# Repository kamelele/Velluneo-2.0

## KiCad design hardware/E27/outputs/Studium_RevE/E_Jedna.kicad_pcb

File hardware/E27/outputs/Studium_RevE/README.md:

# Velluneo E27 · Rev E · studium gabarytów zasilacza

Dwa układy rozmieszczenia wykonane w KiCad na podstawie elektrycznej Rev D. Oba zachowują wartości i połączenia oryginalnych elementów. [Rev D 96 × 34 mm z plikami do wyceny JLCPCB](../Zasilacz_RevD_JLCPCB/README.md) pozostaje jako punkt odniesienia i wersja rezerwowa.

## Jedna płytka

**74 × 32 mm**, czyli ok. **27% mniej powierzchni** niż Rev D. Wszystkie 93 obrysy, łącznie z punktami testowymi, zmieściły się na dwóch stronach z tymi samymi obudowami. Pas pomiędzy padami sieci pierwotnych i wtórnych w rzucie na oś X ma **8,2 mm**. Pole miedzi odprowadzające ciepło trzeba zaprojektować ponownie wraz ze ścieżkami. [Płytka w KiCad](E_Jedna.kicad_pcb)

## Dwie płytki

- **57 × 32 mm, moc.** Wejście 230 V, przetwornica i transformator, prostownik wtórny D7 oraz kondensator wyjściowy C6. D7 i C6 pozostają na tej samej płytce co transformator. J101 wyprowadza S_RAW i S_RTN za układem pomiaru prądu. Pas między padami P/S wynosi 8,2 mm. [Płytka mocy w KiCad](E_Moc.kicad_pcb) · [Podgląd 3D](Podglady/RevE_plytka_mocy.png)
- **30 × 26 mm, sterowanie.** J102 przyjmuje wyłącznie wtórne 26 V i jego powrót. Na tej płytce są eFuse, dwa regulatory prądu, pomiar K1/K2, zatrzask zwarciowy, blokady i punkty testowe. J101/J102 mają zgodne przypisanie: pad 1 S_RAW, pad 2 S_RTN. Docelowy przewód i jego odciążenie wymagają projektu wraz z korpusem. [Płytka sterowania w KiCad](E_Sterowanie.kicad_pcb) · [Podgląd 3D](Podglady/RevE_plytka_sterowania.png)

Podział skraca najdłuższą płytkę o 17 mm względem wariantu jednopłytkowego. Łączna powierzchnia laminatu to 2604 mm² wobec 2368 mm² jednej płytki, czyli około 10% więcej. Zyskiem jest możliwość niezależnego rozmieszczenia części mocy i sterowania. Przy ułożeniu warstwowym trzeba sprawdzić odstęp pomiędzy sieciowymi obszarami i płytką sterowania w trzech wymiarach, przestrzeń na wiązkę i chłodzenie. Wycena wymagałaby dwóch projektów PCB, a dwustronne obsadzenie każdego obrysu osobnej weryfikacji panelu. [JLCPCB PCBA](https://jlcpcb.com/capabilities/pcb-assembly-capabilities)

## Co ogranicza zejście do 38 × 17 × 15 mm

Przyjęty transformator EE16 ma obwiednię montażową ok. 17,2 × 16,2 mm. W zachowanej orientacji i z 0,75 mm rezerwy od krawędzi po obu stronach sam potrzebuje około 17,7 mm szerokości. Poza transformatorem trzeba zmieścić obudowy po obu stronach bariery i zapewnić miejsce na bezpieczne prowadzenie ścieżek. Pionowo ustawiony warystor TMOV14 może wymagać do 22 mm nad PCB przy prostych wyprowadzeniach. Zmniejszanie obrysu z tym samym zestawem części nie rozwiązuje wysokości. [Obwiednia T1](E27.pretty/EE16_6pins_RFQ.kicad_mod) · [Wymiary TMOV, str. 6](https://www.littelfuse.com/assetdocs/varistors-tmov-datasheet?assetguid=bd475732-1071-4352-b8aa-f78b0007eb05)

Przy sztywnym celu 38 × 17 × 15 mm kolejny krok to wstępny dobór węższego i niższego transformatora wraz z izolacją oraz sprawdzenie ułożenia warystora i kondensatorów. Rozmieszczenie płytki mocy zależy od tych danych. Jeżeli korpus daje dwie oddzielne przestrzenie, punktem wyjścia do tej próby jest wariant z dwiema płytkami. Na makietach nie wykonano trasowania, wypełnień cieplnych, pomiarów ani eksportu do zamówienia. [Kontrola rozmieszczenia i przypisań pinów](Kontrola_RevE.md)

## Podglądy 3D

Dwie płytki we wspólnej scenie KiCad, w dwóch ujęciach wzorowanych na prezentacji JLCPCB. Oznaczenia i obrysy montażowe dodano na potrzeby podglądu. Widok bez elementów pokazuje rzeczywiste pady rozmieszczenia Rev E. Ścieżki są na dalszym etapie projektu. [Obie płytki z elementami](Podglady/RevE_JLC_obsadzone.png) · [Obie płytki z góry](Podglady/RevE_JLC_widok_PCB.png) · [Wzorzec JLCPCB](https://jlcpcb.com/blog/kicad-mcp-how-to-design-a-pcb-with-claude-code)

Poprzednie modele niestandardowych obudów w Rev D były prostymi bryłami zastępczymi. Dodałem własne modele do podglądu, z kształtem korpusów i wyprowadzeń. Obejmują m.in. warystor, kondensator Y1, dławik, kondensator SMD, bezpiecznik, mostek prostowniczy i układy scalone. Model transformatora odwzorowuje przyjętą obwiednię i układ sześciu wyprowadzeń, a wygląd rdzenia i uzwojenia pozostaje orientacyjny do wyboru dostawcy. Modele i materiały służą do wizualizacji. Do sprawdzenia mechaniki obowiązują rysunki wymiarowe i próbki komponentów. [Nichicon C6](https://www.nichicon.com/en-us/part/ucm1h471mnj1ms/2563/) · [Würth L1](https://www.we-online.com/components/products/datasheet/768772102.pdf) · [Vishay CY1](https://www.vishay.com/docs/23102/440lseries.pdf) · [Podgląd na stronie JLCPCB](https://jlcpcb.com/blog/kicad-mcp-how-to-design-a-pcb-with-claude-code)

[Rev D z nowymi modelami od góry](Podglady/RevD_nowe_modele_gora.png) · [Rev D od spodu](Podglady/RevD_nowe_modele_dol.png)

Z katalogu `hardware/E27` polecenie `work/export_reve.ps1` odtwarza modele 3D, podglądy i raporty. Opcja `-Rebuild` odtwarza również rozmieszczenie z pliku Rev D.

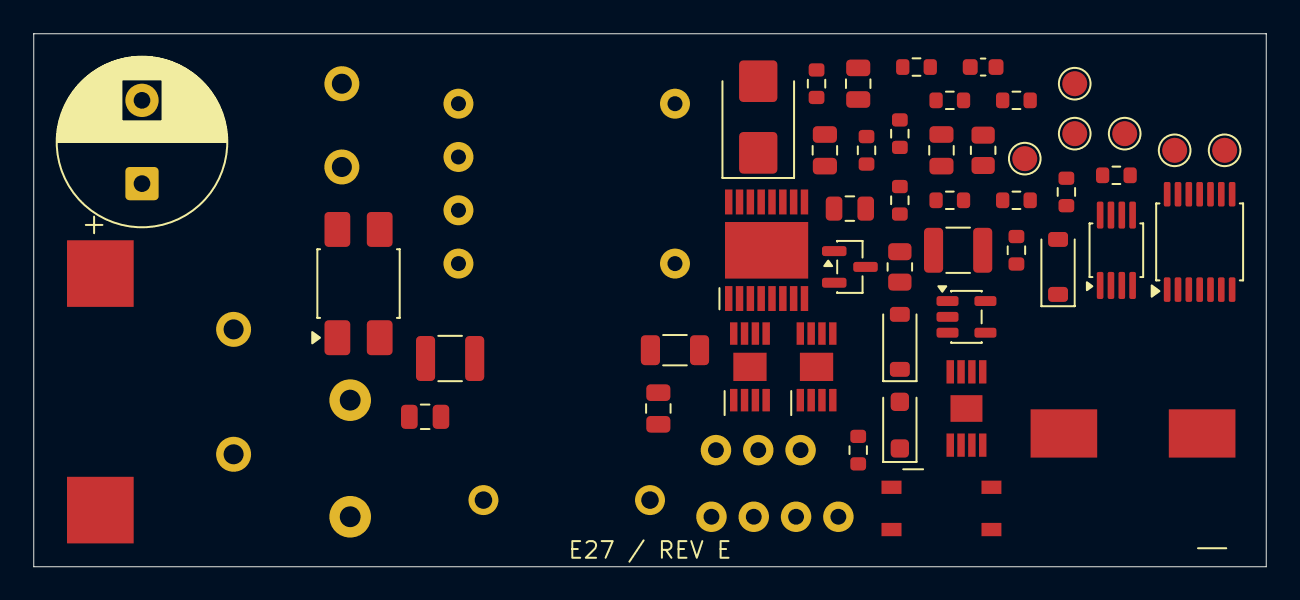
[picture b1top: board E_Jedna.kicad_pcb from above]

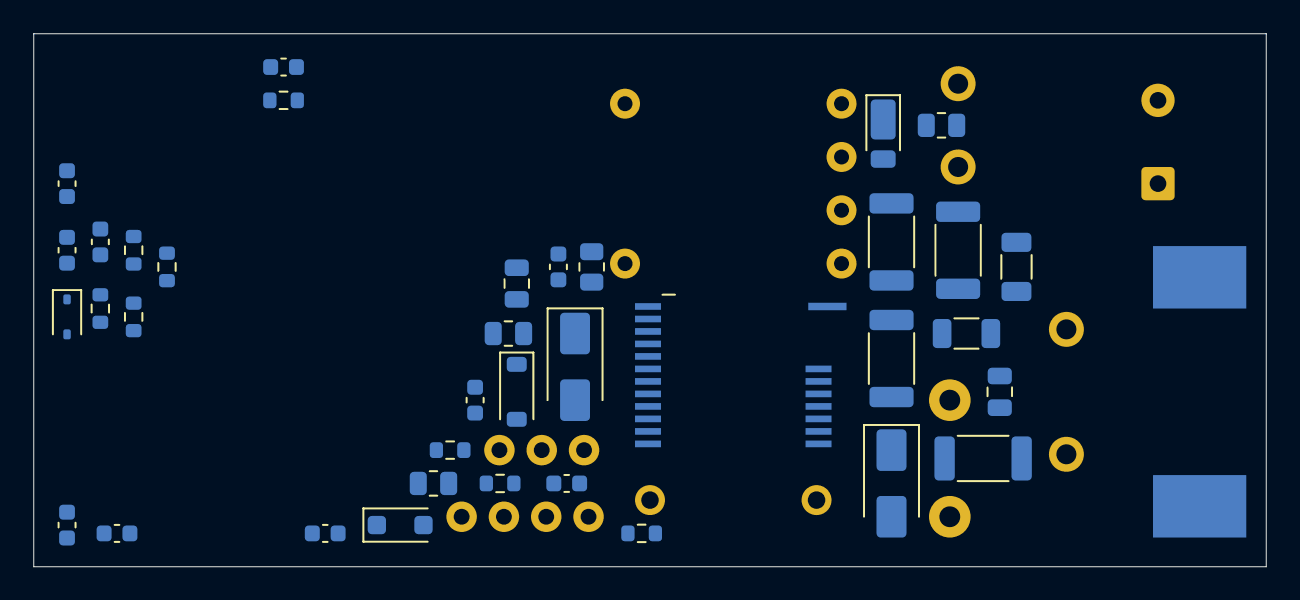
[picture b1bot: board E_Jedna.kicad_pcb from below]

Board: 2 copper layers, 74.0 x 32.0 mm, 93 parts (38 on the bottom side), 51 nets, no tracks yet.

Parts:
BR1: MB10S; OnSemi_751EP_SOIC-4_3.9x4.725mm_P2.54mm
C1: 100n / 630V; C_1210_3225Metric
C2: 10u / 450V; CP_Radial_D10.0mm_P5.00mm
C3: 1.5n / 200V; C_0805_2012Metric
C4: 22u / 35V; C_1206_3216Metric
C5: 470n / 50V; C_0805_2012Metric
C6: 470u / 50V; UCM_12p5
C7: 68p / 200V; C_0603_1608Metric
C8: 330p; C_0603_1608Metric
C9: 2.2u / 25V; C_1206_3216Metric
C10, C11, C13, C14, C15: 100n / 50V; C_0805_2012Metric
C12: 47n; C_0603_1608Metric
C101: 2.2u / 100V; C_1210_3225Metric
C102: 10u / 25V; C_0805_2012Metric
C103, C106, C108: 10n; C_0603_1608Metric
C104, C105: 220n / 50V X7R 10%; C_0603_1608Metric
C107, C109, C110: 100n; C_0603_1608Metric
CY1: 2.2n Y1; CY1_10mm
D5: US1J; D_SMA
D6: DFLU1200; D_PowerDI-123
D7: SK3200B; D_SMB
D8: US1B; D_SMA
D9: BAV21W; D_SOD-123
D101: BAT54WS; D_SOD-323
D102, D103: PMEG6010CEH; D_SOD-123F
F1: T 500 mA / 277 VAC; Schurter_UMT_H
J1: 230 VAC; Mains_L_N
J2: S1+TH / S2; Harness_4pos
J3: A+ / KA / KB; Harness_3pos
L1: 1mH; Wurth_TI_HV_8
Q1: MMBT5551; SOT-23
R1: 22R / 1.1W fusible; AC01_CS_WSZ
R2, R3: 510k HV; R_2010_5025Metric
R4: 1M; R_1206_3216Metric
R5, R19: 10k; R_0805_2012Metric
R6, R7: 2.2M HV; R_2010_5025Metric
R8: 47R; R_0805_2012Metric
R9: 0.11R; R_0805_2012Metric
R10: 110k 0.1%; R_0603_1608Metric
R11: 5.62k 0.1%; R_0603_1608Metric
R12: 2.2k; R_0805_2012Metric
R13: 100R; R_0805_2012Metric
R14: 226k 0.1%; R_0603_1608Metric
R15: 10k 0.1%; R_0603_1608Metric
R16: 30.1k 1%; R_0603_1608Metric
R17, R18: 10k; R_0603_1608Metric
R20, R21: 5.90k 1%; R_0603_1608Metric
R101, R109: 22k; R_0603_1608Metric
R102: 2.2k; R_0603_1608Metric
R103: 133k 0.1%; R_0603_1608Metric
R104, R106, R108: 22k 0.1%; R_0603_1608Metric
R105, R107: 330k 0.1%; R_0603_1608Metric
R110: 100k; R_0603_1608Metric
R111: 249R 1%; R_0603_1608Metric
R112: 100k 1%; R_0603_1608Metric
RV1: 275 VAC; TMOV14
T1: EE16 84:23:13; EE16_6pins_RFQ
TP101: S_RTN; TestPoint_Pad_D1.5mm
TP102: V3V3; TestPoint_Pad_D1.5mm
TP103: PG; TestPoint_Pad_D1.5mm
TP104: CLR_N; TestPoint_Pad_D1.5mm
TP105: PERMIT; TestPoint_Pad_D1.5mm
TP106: S_EN; TestPoint_Pad_D1.5mm
U1: LYT6073C-TL; InSOP_24D
U2: TPS26600PWPR; PWP0016A
U3, U4: AL5812MP-13; E27_Al5812_MSOP
U101: TPS7A1633; TPS7A16_DGN
U102: TLV1702; MSOP-8_3x3mm_P0.65mm
U103: SN74HCS74; TSSOP-14_4.4x5mm_P0.65mm
U104: SN74LVC1G132; SOT-23-5
U105: AQY212GS; AQY212GS_SOP4
ZD1: 18V; D_SOD-123
ZD2: 27V; D_SOD-123

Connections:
/CLK: C108.1, R110.2, U103.3
/CLR_N: D101.2, R109.2, TP104.1, U102.1, U102.7, U103.1
/DELAY: C103.1, U101.7
/EN_SERIES: R112.1, U105.3
/K1_F: C104.1, R105.2, R106.1, U102.2
/K2_F: C105.1, R107.2, R108.1, U102.6
/LDO_IN: C101.1, D102.1, D103.1, U101.5, U101.8
/LED_A: R111.2, U105.1
/LED_SINK: U104.4, U105.2
/PERMIT: TP105.1, U103.5, U104.2
/PG: D101.1, R101.2, R110.1, TP103.1, U101.3, U104.1
/P_0: BR1.2, C1.2, C2.2, C4.2, C5.2, R3.2, T1.4, U1.16, U1.17, U1.18, U1.19
/P_AUX: D6.2, T1.3
/P_BIAS: C4.1, D6.1, R5.1
/P_BLEED: R2.2, R3.1
/P_BPP: C5.1, R5.2, U1.14
/P_BR: BR1.1, C1.1, L1.1
/P_BULK: C2.1, C3.2, CY1.1, L1.2, R2.1, R4.2, R6.1, T1.2
/P_CL: C3.1, D5.1, R4.1
/P_D: D5.2, T1.1, U1.24
/P_L: F1.1, J1.1
/P_LF: F1.2, R1.1
/P_LR: BR1.3, R1.2, RV1.1
/P_N: BR1.4, J1.2, RV1.2
/P_V: R7.2, U1.13
/P_VMID: R6.2, R7.1
/REF: C106.1, R103.2, R104.1, U102.3, U102.5
/S1_RETURN: J2.2, U105.4
/S_BPS: C9.1, D9.1, U1.4
/S_EN: R18.1, R112.2, TP106.1, U2.7
/S_ENFEED: J2.1, R17.2
/S_FB: C8.1, R10.2, R11.1, U1.3
/S_FUSED: C13.1, J2.3, U2.15, U2.16
/S_FWD: C7.1, R8.2, U1.7
/S_GND: C6.2, C7.2, C8.2, C9.2, C10.2, D7.2, D8.1, R9.2, R11.2, U1.2, U1.5, ZD1.2
/S_ILIM: R16.1, U2.11
/S_LED_KA: J3.2, R105.1, U3.8
/S_LED_KB: J3.3, R107.1, U4.8
/S_LED_PLUS: C14.1, C15.1, J2.4, J3.1, R19.1, U3.1, U4.1
/S_OVA: R13.1, ZD2.2
/S_OVB: D9.2, R13.2
/S_OVP: R14.2, R15.1, U2.5
/S_RAW: C6.1, C11.1, CY1.2, D102.2, Q1.3, R10.1, R12.1, R14.1, R17.1, T1.5, U2.1, U2.2, ZD2.1
/S_RTN: C11.2, C12.2, C13.2, C14.2, C15.2, C101.2, C102.2, C103.2, C104.2, C105.2, C106.2, C107.2, C108.2, C109.2, C110.2, D8.2, R9.1, R15.2, R16.2, R18.2, R19.2, R20.2, R21.2, R102.2, R104.2, R106.2, R108.2, TP101.1, U1.1, U2.3, U2.8, U2.9, U2.17, U3.5, U3.9, U4.5, U4.9, U101.4, U101.9, U102.4, U103.7, U103.11, U103.12, U103.13, U104.3
/S_SET_A: R20.1, U3.4
/S_SET_B: R21.1, U4.4
/S_SLEW: C12.1, U2.12
/S_SW: D7.1, R8.1, T1.6
/S_VO: C10.1, Q1.2, U1.6
/S_Z18: Q1.1, R12.2, ZD1.1
/V3V3: C102.1, C107.1, C109.1, C110.1, D103.2, R101.1, R102.1, R103.1, R109.1, R111.1, TP102.1, U101.1, U102.8, U103.2, U103.4, U103.10, U103.14, U104.5

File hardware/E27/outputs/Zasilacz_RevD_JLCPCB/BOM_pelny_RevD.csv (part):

Ref,Nazwa i funkcja,Parametry,Producent,MPN,Footprint,LCSC Part #,Ilość na PCB,Zakup alternatywny,Cena jednostkowa prototyp / seria,Koszt pozycji prototyp / seria,Dostępność,Zamiennik do weryfikacji,Strona,Plan montażu,Źródło,Uwagi
J1,Przewody L i N z E27,230 VAC,,,E27:Mains_L_N,,1,Wycena dostawcy / RFQ,Do wyceny,Do wyceny,Brak potwierdzonego kodu w katalogu montażowym,,Top,Montaż wiązki po obsadzeniu,,THT / wiązka. Uzgodnić oddzielny montaż. Stałe lutowanie i odciążenie przewodów.
F1,Bezpiecznik zwłoczny,T 500 mA / 277 VAC,Schurter,3403.0271.23,E27:Schurter_UMT_H,,1,DigiKey 9094779,Do wyceny,Do wyceny,Brak potwierdzonego kodu w katalogu montażowym,,Bottom,RFQ / dobrać i zweryfikować dokładny MPN,https://www.digikey.com/en/products/detail/schurter-inc/3403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,"UMT-H. 1,5 kA przy 277 VAC UL albo przy 250 VAC IEC, warunki z karty. Wymaga testu zdolności wyłączania całego zespołu."
RV1,Ogranicznik przepięć z odcięciem termicznym,275 VAC,Littelfuse,TMOV14RP275E,E27:TMOV14,C1528070,1,Littelfuse / DigiKey,Do wyceny,Do wyceny,Zapas montażowy JLCPCB do potwierdzenia,iTMOV14RP275M z adaptacją footprintu i badaniem,Top,Osobne uzgodnienie montażu THT,https://jlcpcb.com/partdetail/Littelfuse-TMOV14RP275E/C1528070,"Za R1. Budżet wysokości 22 mm dla prostych wyprowadzeń. Sprawdzić udar, ciągłe przepięcie i rozłączenie termiczne."
R1,Ograniczenie prądu udarowego,22R / 1.1W fusible,Vishay,AC01000902209JBMCS,E27:AC01_CS_WSZ,,1,DigiKey 28721869,Do wyceny,Do wyceny,Brak potwierdzonego kodu w katalogu montażowym,,Top,RFQ / dobrać i zweryfikować dokładny MPN,https://www.digikey.com/en/products/detail/vishay-beyschlag-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,"AC01-CS WSZ. Potwierdzić obrys, impuls rozruchowy, temperaturę i koordynację z F1."
C1,Bocznik HF za mostkiem,100n / 630V,TDK,C3225X7T2J104KT000N,Capacitor_SMD:C_1210_3225Metric,C342668,1,LCSC / Mouser,Do wyceny,Do wyceny,Zapas montażowy JLCPCB do potwierdzenia,1210 100 nF 630 V po sprawdzeniu charakterystyki DC,Top,Do importu i sprawdzenia w JLCPCB,https://www.lcsc.com/product-detail/C342668.html,"SMT do potwierdzenia w JLCPCB po importowaniu BOM. X7T, sprawdzić pojemność pod napięciem DC."
L1,Dławik filtra różnicowego,1mH,Würth Elektronik,768772102,E27:Wurth_TI_HV_8,C7194056,1,DigiKey 2682552,Do wyceny,Do wyceny,Zapas JLCPCB do potwierdzenia. Poprzedni odczyt 0.,,Top,Osobne uzgodnienie montażu THT,https://jlcpcb.com/partdetail/WurthElektronik-768772102/C7194056,"1 mH, 0,5 A, Isat 0,55 A typ. Brak ekranu. Sprawdzić EMI, udar i rozgrzanie w rzeczywistym układzie."
C2,Magazyn energii na szynie HV,10u / 450V,Rubycon,450BXW10MEFR10X16,Capacitor_THT:CP_Radial_D10.0mm_P5.00mm,,1,DigiKey 6049847,Do wyceny,Do wyceny,Brak potwierdzonego kodu w katalogu montażowym,,Top,Osobne uzgodnienie montażu THT,https://www.digikey.com/es/products/detail/rubycon/450BXW10M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,"Ø10 mm × 16 mm nominalnie. 18 mm maks. nad PCB, raster 5 mm. 10 000 h przy 105°C."
R2,Rozładowanie szyny HV,510k HV,Vishay,CRCW2010510KFKEF,Resistor_SMD:R_2010_5025Metric,C4245382,1,Wycena dostawcy / RFQ,Do wyceny,Do wyceny,Zapas montażowy JLCPCB do potwierdzenia,,Bottom,Do importu i sprawdzenia w JLCPCB,https://www.lcsc.com/product-detail/C4245382.html,"Vishay CRCW2010, 400 V DC/RMS wg karty. Potwierdzić udar i rozkład napięcia. SMT do potwierdzenia w JLCPCB po importowaniu BOM. Dwa rezystory szeregowe, potwierdzić napięcie pracy, dobrać tolerancję i udar."
R3,Rozładowanie szyny HV,510k HV,Vishay,CRCW2010510KFKEF,Resistor_SMD:R_2010_5025Metric,C4245382,1,Wycena dostawcy / RFQ,Do wyceny,Do wyceny,Zapas montażowy JLCPCB do potwierdzenia,,Bottom,Do importu i sprawdzenia w JLCPCB,https://www.lcsc.com/product-detail/C4245382.html,"Vishay CRCW2010, 400 V DC/RMS wg karty. Potwierdzić udar i rozkład napięcia. SMT do potwierdzenia w JLCPCB po importowaniu BOM."
T1,Transformator flyback 1.2 mH ±8%,EE16 84:23:13,,,E27:EE16_6pins_RFQ,,1,Wycena dostawcy / RFQ,Do wyceny,Do wyceny,Brak potwierdzonego kodu w katalogu montażowym,,Top,RFQ transformatora EE16 i montaż THT,,"THT / wiązka. Uzgodnić oddzielny montaż. RFQ. Potwierdzić karkas, pinout, TIW, odstępy i badania. Zwroty w raporcie."
C3,Kondensator ogranicznika RCD,1.5n / 200V,KYOCERA AVX,08052C152KAT2A,Capacitor_SMD:C_0805_2012Metric,,1,"DigiKey / Mouser, wyszukiwanie po MPN",Do wyceny,Do wyceny,Brak potwierdzonego kodu w katalogu montażowym,"Element równoważny po sprawdzeniu wartości, obudowy, temperatury i parametrów impulsowych",Bottom,RFQ / dobrać i zweryfikować dokładny MPN,,SMT do potwierdzenia w JLCPCB po importowaniu BOM.
R4,Rezystor ogranicznika RCD,1M,Panasonic,ERJ-8GEYJ105V,Resistor_SMD:R_1206_3216Metric,C278663,1,"DigiKey / Mouser, wyszukiwanie po MPN",Do wyceny,Do wyceny,Zapas montażowy JLCPCB do potwierdzenia,"Element równoważny po sprawdzeniu wartości, obudowy, temperatury i parametrów impulsowych",Bottom,Do importu i sprawdzenia w JLCPCB,https://www.lcsc.com/product-detail/C278663.html,SMT do potwierdzenia w JLCPCB po importowaniu BOM.
D5,Dioda ogranicznika RCD,US1J,Diodes Inc.,US1J-13-F,Diode_SMD:D_SMA,C85095,1,"DigiKey / Mouser, wyszukiwanie po MPN",Do wyceny,Do wyceny,Zapas montażowy JLCPCB do potwierdzenia,"Element równoważny po sprawdzeniu wartości, obudowy, temperatury i parametrów impulsowych",Bottom,Do importu i sprawdzenia w JLCPCB,https://www.lcsc.com/product-detail/C85095.html,"SMT do potwierdzenia w JLCPCB po importowaniu BOM. Potwierdzić impulsy, temperaturę i rzeczywiste VDS."
D6,Prostownik uzwojenia pomocniczego,DFLU1200,Diodes Inc.,DFLU1200-7,Diode_SMD:D_PowerDI-123,,1,"DigiKey / Mouser, wyszukiwanie po MPN",Do wyceny,Do wyceny,Brak potwierdzonego kodu w katalogu montażowym,"Element równoważny po sprawdzeniu wartości, obudowy, temperatury i parametrów impulsowych",Bottom,RFQ / dobrać i zweryfikować dokładny MPN,,SMT do potwierdzenia w JLCPCB po importowaniu BOM.
C4,Zasobnik zasilania BPP,22u / 35V,TDK,C3216X5R1V226M160AC,Capacitor_SMD:C_1206_3216Metric,C69612,1,"DigiKey / Mouser, wyszukiwanie po MPN",Do wyceny,Do wyceny,Zapas montażowy JLCPCB do potwierdzenia,"Element równoważny po sprawdzeniu wartości, obudowy, temperatury i parametrów impulsowych",Bottom,Do importu i sprawdzenia w JLCPCB,https://www.lcsc.com/product-detail/C69612.html,SMT do potwierdzenia w JLCPCB po importowaniu BOM.
R5,Ograniczenie prądu zasilania BPP,10k,Panasonic,ERJ-6ENF1002V,Resistor_SMD:R_0805_2012Metric,C169253,1,"DigiKey / Mouser, wyszukiwanie po MPN",Do wyceny,Do wyceny,Zapas montażowy JLCPCB do potwierdzenia,"Element równoważny po sprawdzeniu wartości, obudowy, temperatury i parametrów impulsowych",Bottom,Do importu i sprawdzenia w JLCPCB,https://www.lcsc.com/product-detail/C169253.html,SMT do potwierdzenia w JLCPCB po importowaniu BOM.
R6,Pomiar napięcia szyny V,2.2M HV,Vishay,CRCW20102M20FKEF,Resistor_SMD:R_2010_5025Metric,C4263855,1,Wycena dostawcy / RFQ,Do wyceny,Do wyceny,Zapas montażowy JLCPCB do potwierdzenia,,Bottom,Do importu i sprawdzenia w JLCPCB,https://www.lcsc.com/product-detail/C4263855.html,"Vishay CRCW2010, 400 V DC/RMS wg karty. Potwierdzić udar i rozkład napięcia. SMT do potwierdzenia w JLCPCB po importowaniu BOM."
R7,Pomiar napięcia szyny V,2.2M HV,Vishay,CRCW20102M20FKEF,Resistor_SMD:R_2010_5025Metric,C4263855,1,Wycena dostawcy / RFQ,Do wyceny,Do wyceny,Zapas montażowy JLCPCB do potwierdzenia,,Bottom,Do importu i sprawdzenia w JLCPCB,https://www.lcsc.com/product-detail/C4263855.html,"Vishay CRCW2010, 400 V DC/RMS wg karty. Potwierdzić udar i rozkład napięcia. SMT do potwierdzenia w JLCPCB po importowaniu BOM."
C5,Odprzęganie BPP,470n / 50V,Murata,GRM21BR71H474KA88L,Capacitor_SMD:C_0805_2012Metric,C86043,1,"DigiKey / Mouser, wyszukiwanie po MPN",Do wyceny,Do wyceny,Zapas montażowy JLCPCB do potwierdzenia,"Element równoważny po sprawdzeniu wartości, obudowy, temperatury i parametrów impulsowych",Top,Do importu i sprawdzenia w JLCPCB,https://www.lcsc.com/product-detail/C86043.html,SMT do potwierdzenia w JLCPCB po importowaniu BOM.
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
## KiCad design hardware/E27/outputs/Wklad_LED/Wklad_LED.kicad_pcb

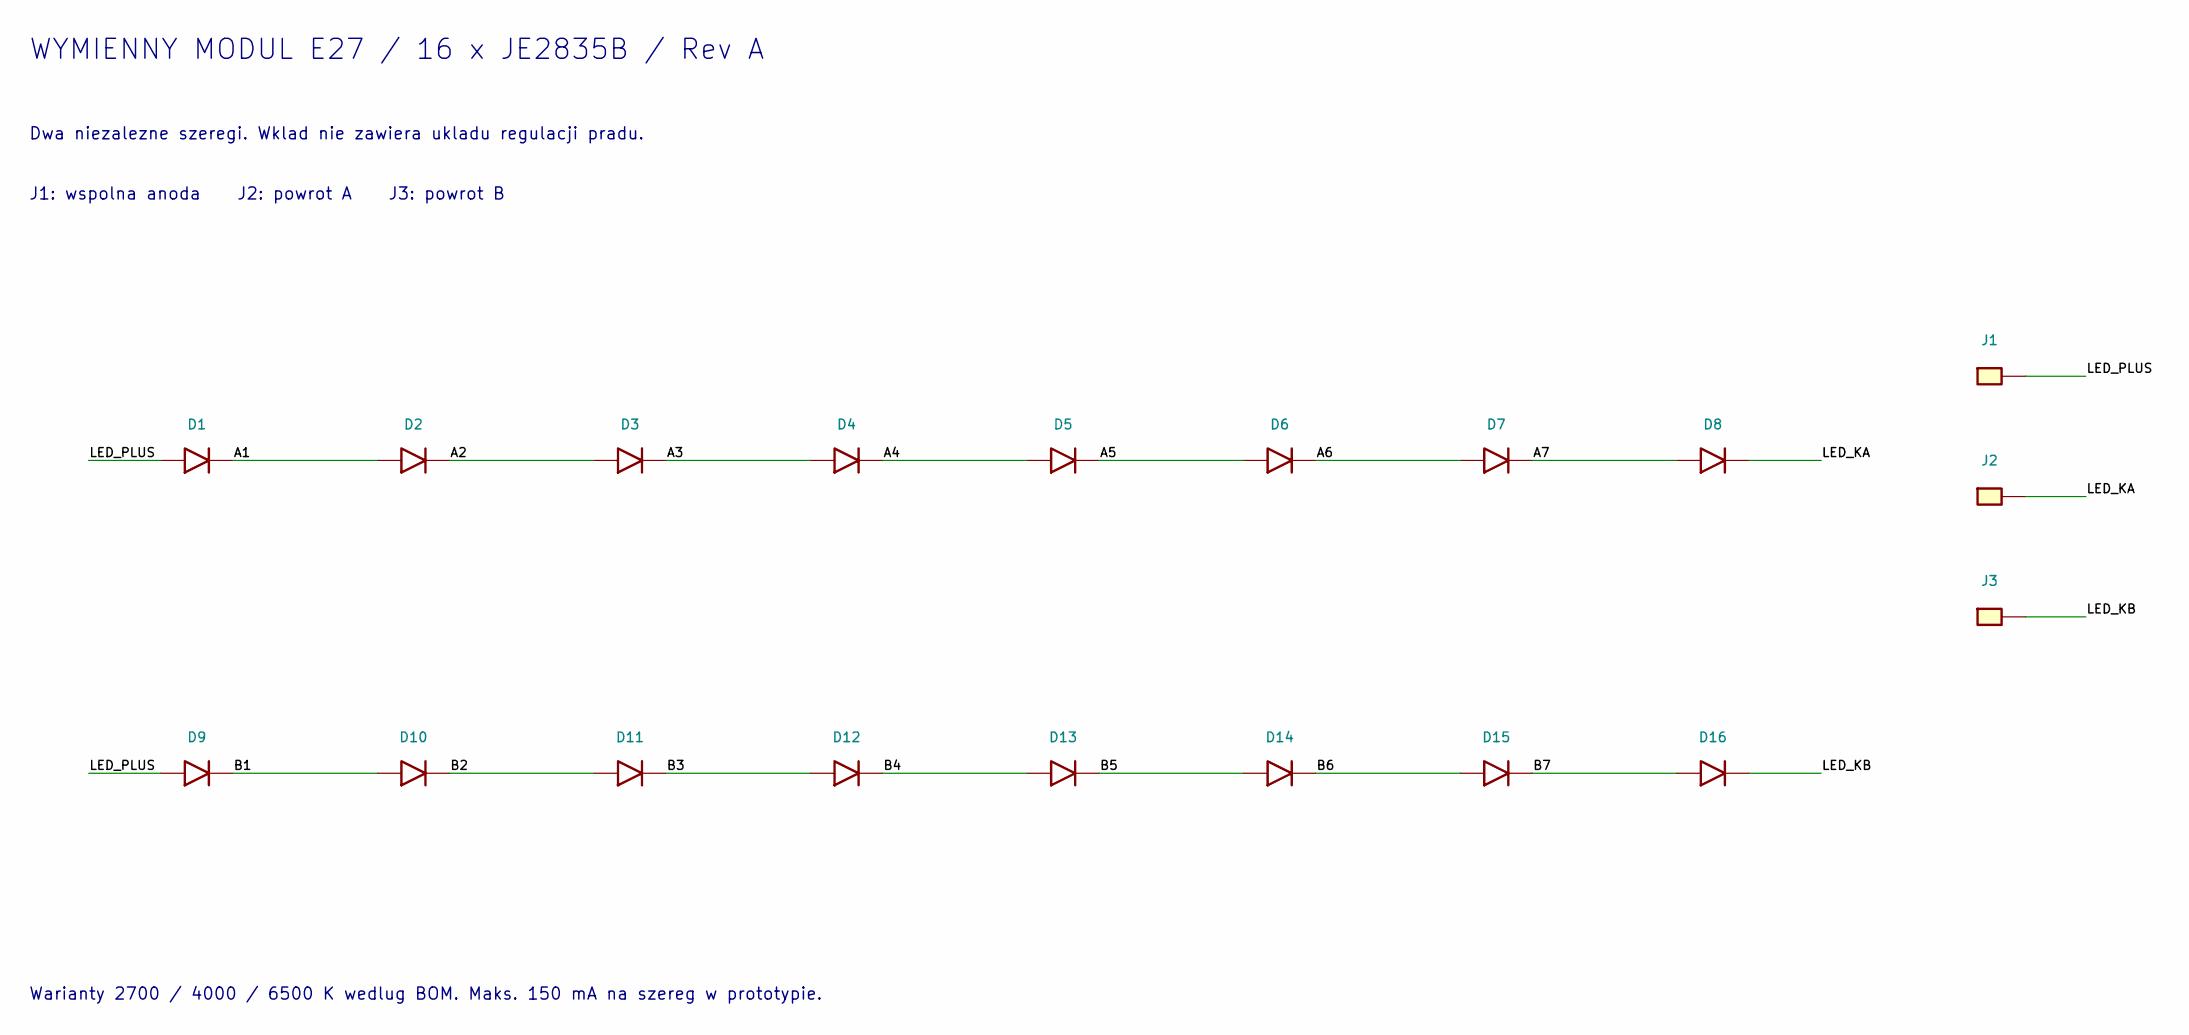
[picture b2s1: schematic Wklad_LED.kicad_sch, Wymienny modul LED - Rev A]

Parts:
D1, D2, D3, D4, D5, D6, D7, D8, D9, D10, D11, D12, D13, D14, D15, D16: JE2835B; Cree_JE2835B
J1: LED_PLUS; SpringPad
J2: LED_KA; SpringPad
J3: LED_KB; SpringPad

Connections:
/A1: D1.1 (K), D2.2 (A)
/A2: D2.1 (K), D3.2 (A)
/A3: D3.1 (K), D4.2 (A)
/A4: D4.1 (K), D5.2 (A)
/A5: D5.1 (K), D6.2 (A)
/A6: D6.1 (K), D7.2 (A)
/A7: D7.1 (K), D8.2 (A)
/B1: D9.1 (K), D10.2 (A)
/B2: D10.1 (K), D11.2 (A)
/B3: D11.1 (K), D12.2 (A)
/B4: D12.1 (K), D13.2 (A)
/B5: D13.1 (K), D14.2 (A)
/B6: D14.1 (K), D15.2 (A)
/B7: D15.1 (K), D16.2 (A)
/LED_KA: D8.1 (K), J2.1
/LED_KB: D16.1 (K), J3.1
/LED_PLUS: D1.2 (A), D9.2 (A), J1.1

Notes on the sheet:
WYMIENNY MODUL E27 / 16 x JE2835B / Rev A
Dwa niezalezne szeregi. Wklad nie zawiera ukladu regulacji pradu.
J1: wspolna anoda J2: powrot A J3: powrot B
Warianty 2700 / 4000 / 6500 K wedlug BOM. Maks. 150 mA na szereg w prototypie.

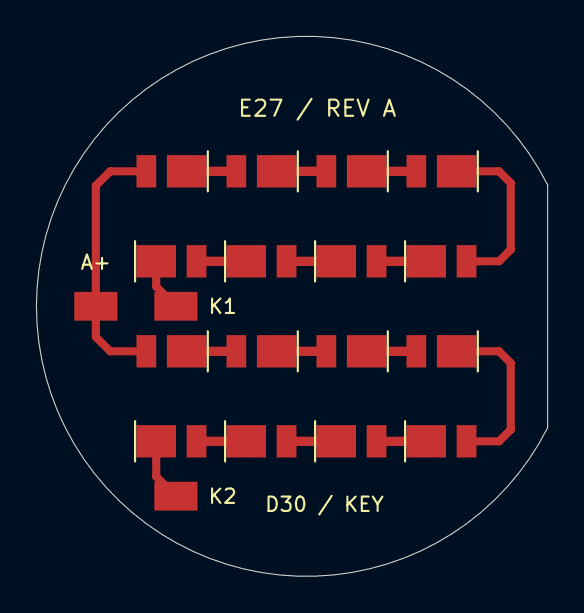
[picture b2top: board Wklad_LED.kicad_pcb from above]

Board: 2 copper layers, 28.4 x 30.0 mm, 19 parts (0 on the bottom side), 17 nets.
